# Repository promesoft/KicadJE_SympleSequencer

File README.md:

# KicadJE_SympleSequencer
Designed to fit the faceplate of a Hexinverter SympleSeq E2 faceplate from Re:Synthesis

# Purpose
1 - Match Hexinverter sch with Resynthesis panel

# Rev 2

# Status - Mouted - testing
## Initial 
| Stage  | Detail | Status |
| ------------- | ------------- | ------------- |
| create material  | sch/pcb | OK  |
| | gerber | OK |
| production  |   | ok |
|  | produced | ok |
|  | delivered | ok |

## Preliminary validation
| Test  | Detail | Status |
| ------------- | ------------- | ------------- |
| Initial Inspection | clock board| ok |
| Initial Inspection | control board | ok  |
| Initial Technical Test |  | 100n capacitors in series w output is replaced w 2k |
| Initial Product Test |  | 100n C101 capacitor parallel w 150k |
| Initial Product Test |  | ongoing |

## Secondary validation
| Test  | Detail | Status |
| ------------- | ------------- |------------- |
| Product Test | CV |  |
| Product Test | Gate | |
| Product Test | Clock internal |  |
| Product Test | Clock in |  |
| Product Test | Clock out |  |
| Product Test | Reset In/Button |  |
| Product Test | Hold In/Button |  |
| Quality | CV |  |
| Quality | Gate |  |
| Long Term Product Test |  | Good |
| Power Draw |  | 

## Errata
### Errata - clock
#### Series capacitors not working with reset (overloads CD4017)
 - replace w resistors (2k and 9k1 tested and working fine)
#### Hold not working 
 - Either swap R206 100k pullup with 22k-47k and R212 10k with 100k or tie hold to +12v works
### Errata - control
#### 

## Issues and Notes
### Clock
1 - diodes for hold input  
2 - diodes for reset input  
3 - Gate AND Clock for gate output to reset between gates - consider making a phase adjust for shorter/longer gates  
4 - OPEN resistor from Internal CLK to 4017 clock in (for use with Sequencer A that does not take slave clk input)
### Control
1 - switches still reversed  
2 - diode missing for reset  
3 - consider moving resistors from clk module to control as there is plenty of room  

# Schematics

# Pictures

# Rev 1

# Status - Installed in rack - tweaking
## Initial 
| Stage  | Detail | Status |
| ------------- | ------------- | ------------- |
| create material  | sch/pcb | OK  |
| | gerber | OK |
| production  |   | ok |
|  | produced | ok |
|  | delivered | ok |

## Preliminary validation
| Test  | Detail | Status |
| ------------- | ------------- | ------------- |
| Initial Inspection | clock board| ok - the jacks are 0,5-1mm too far away from the edge |
| Initial Inspection | control board | ok - see errata 3 |
| Initial Technical Test |  | ok |
| Initial Product Test |  | ok |

## Secondary validation
| Test  | Detail | Status |
| ------------- | ------------- |------------- |
| Product Test | CV | ok |
| Product Test | Gate | See errata 4|
| Product Test | Clock internal | ok - a bit slow |
| Product Test | Clock in | ok |
| Product Test | Clock out | ok - could need a buffer |
| Product Test | Reset In/Button | ok |
| Product Test | Hold In/Button | ok - needs debounce |
| Quality | CV | Good |
| Quality | Gate | No good - needs shorter pulses |
| Long Term Product Test |  | Good |
| Power Draw |  | 

## Errata
### Errata - clock
#### 1 - Missing slave clk function (add diode or buffer - consider val of  R204 on master)
#### 4 - Gate signal becomes glide if two adjacent notes are on (never goes to 0V - consider AC couple)
#### 5 - Hold works - but can be a bit jumpy if clocked faster than clk
#### 7 - Hold button needs debounce (47nF?)

### Errata - control
#### 2 - D310 not connected to G8 output
#### 3 - Switches upside down (still works just opposite the faceplate signs)
#### 6 - Switches in reset works one at the time. Mutliselect becomes strange (diode missing)

## Issues and Notes
### Clock
1 - Missing silk on Jacks

2 - 
### Control

## Vital Components
 - CD4017
 - LM555
 - Jack connectors: PJ-324M (important for the footprint)
# Schematics

# Pictures

# Inspiration from 
Counter module in https://github.com/promesoft/KicadJE_EffectsUnit1

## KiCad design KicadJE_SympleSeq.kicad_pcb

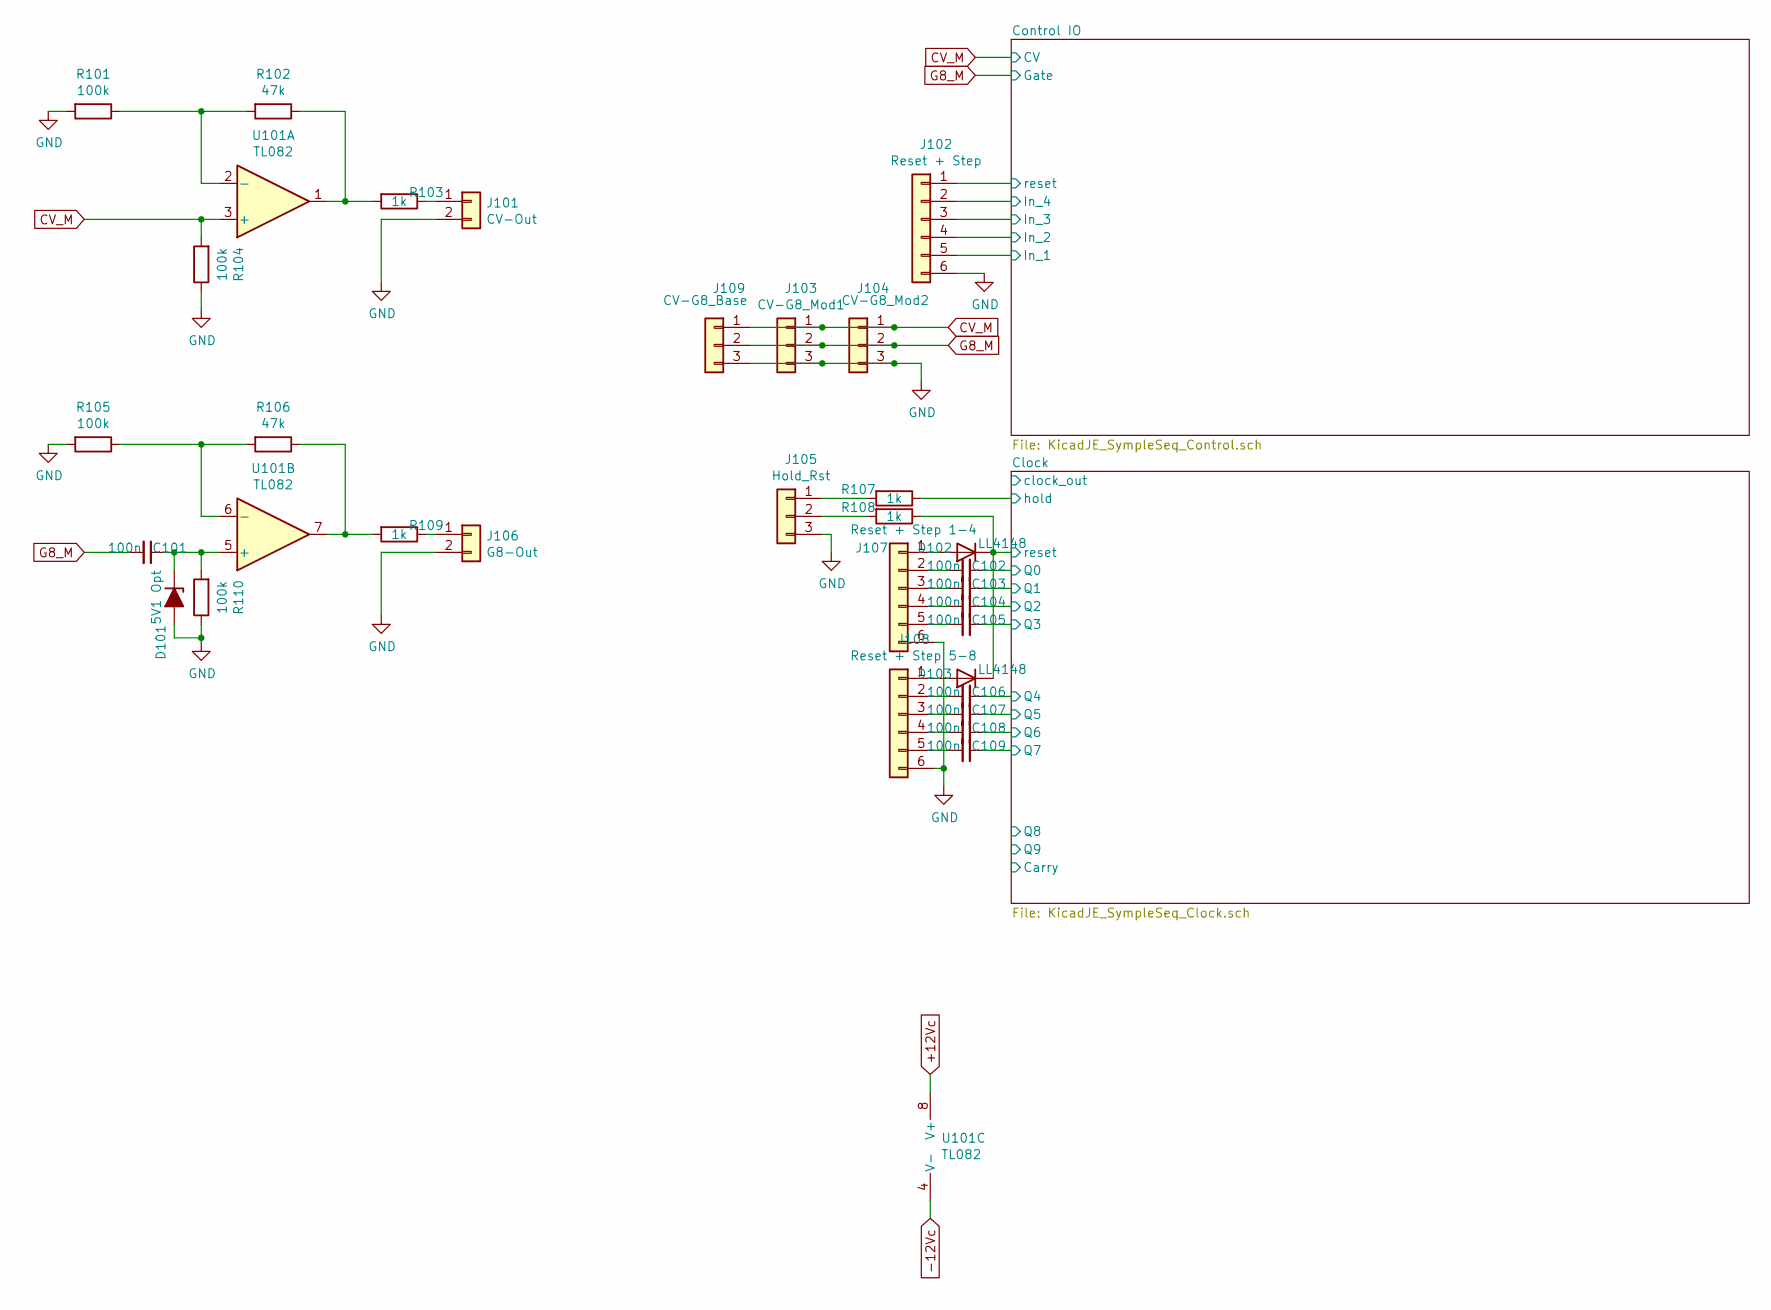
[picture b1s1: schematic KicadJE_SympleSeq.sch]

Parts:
C101, C102, C103, C104, C105, C106, C107, C108, C109: 100n; C_0805_AJ
D101: 5V1 Opt; D_MiniMELF
D102, D103: LL4148; D_MiniMELF
J101: CV-Out; PinHeader_1x02_P2.54mm_Vertical
J102: Reset + Step; PinHeader_1x06_P2.54mm_Vertical
J103: CV-G8_Mod1; PinHeader_1x03_P2.54mm_Vertical
J104: CV-G8_Mod2; PinHeader_1x03_P2.54mm_Vertical
J105: Hold_Rst; PinHeader_1x03_P2.54mm_Vertical
J106: G8-Out; PinHeader_1x02_P2.54mm_Vertical
J107: Reset + Step 1-4; PinHeader_1x06_P2.54mm_Vertical
J108: Reset + Step 5-8; PinHeader_1x06_P2.54mm_Vertical
J109: CV-G8_Base; PinHeader_1x03_P2.54mm_Vertical
R101, R104, R105, R110: 100k; R_0805_AJ
R102, R106: 47k; R_0805_AJ
R103, R107, R108, R109: 1k; R_0805_AJ
U101: TL082; AJ_SO-8_5.3x6.2mm_P1.27mm

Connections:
+12Vc: U101.8 (V+); also elsewhere on the board
-12Vc: U101.4 (V-); also elsewhere on the board
/Clock/Q0: C102.1; also elsewhere on the board
/Clock/Q1: C103.1; also elsewhere on the board
/Clock/Q2: C104.1; also elsewhere on the board
/Clock/Q3: C105.1; also elsewhere on the board
/Clock/Q4: C106.1; also elsewhere on the board
/Clock/Q5: C107.1; also elsewhere on the board
/Clock/Q6: C108.1; also elsewhere on the board
/Clock/Q7: C109.1; also elsewhere on the board
/Clock/hold: R107.1; also elsewhere on the board
/Clock/reset: D102.1 (K), D103.1 (K), R108.1; also elsewhere on the board
/Control IO/In_1: J102.5; also elsewhere on the board
/Control IO/In_2: J102.4; also elsewhere on the board
/Control IO/In_3: J102.3; also elsewhere on the board
/Control IO/In_4: J102.2; also elsewhere on the board
/Control IO/reset: J102.1; also elsewhere on the board
CV_M: J103.1, J104.1, J109.1, R104.2, U101.3 (+); also elsewhere on the board
G8_M: C101.2, J103.2, J104.2, J109.2; also elsewhere on the board
GND: D101.2 (A), J101.2, J102.6, J103.3, J104.3, J105.3, J106.2, J107.6, J108.6, J109.3, R101.2, R104.1, R105.2, R110.1; also elsewhere on the board
unnamed: C101.1, D101.1 (K), R110.2, U101.5 (+)
unnamed: C102.2, J107.2
unnamed: C103.2, J107.3
unnamed: C104.2, J107.4
unnamed: C105.2, J107.5
unnamed: C106.2, J108.2
unnamed: C107.2, J108.3
unnamed: C108.2, J108.4
unnamed: C109.2, J108.5
unnamed: D102.2 (A), J107.1
unnamed: D103.2 (A), J108.1
unnamed: J101.1, R103.1
unnamed: J105.1, R107.2
unnamed: J105.2, R108.2
unnamed: J106.1, R109.1
unnamed: R101.1, R102.2, U101.2 (-)
unnamed: R102.1, R103.2, U101.1
unnamed: R105.1, R106.2, U101.6 (-)
unnamed: R106.1, R109.2, U101.7

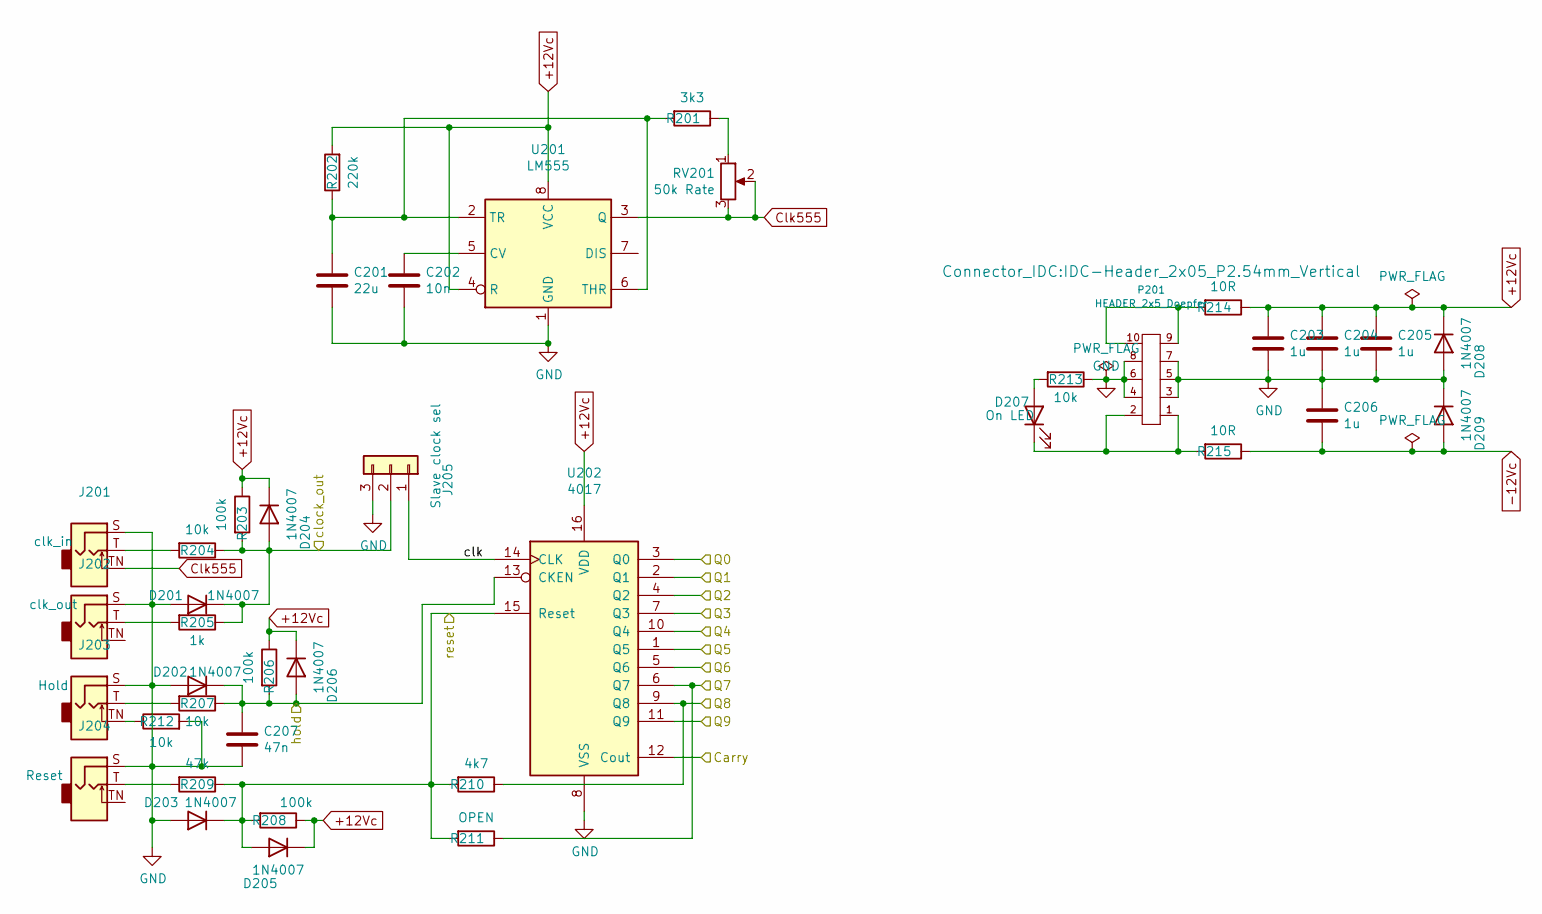
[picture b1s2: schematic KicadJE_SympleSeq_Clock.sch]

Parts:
C201: 22u; C_1206_3216Metric_Pad1.42x1.75mm_HandSolder
C202: 10n; C_0805_AJ
C203, C205: 1u; C_0805_AJ
C204, C206: 1u; C_1206_3216Metric_Pad1.42x1.75mm_HandSolder
C207: 47n; C_0805_AJ
D201, D202, D203, D204, D205, D206, D208, D209: 1N4007; D_MiniMELF
D207: On LED; D_0805_AJ
J201: clk_in; Jack_3.5mm_Ledino_KB3SPRS_Horizontal
J202: clk_out; Jack_3.5mm_Ledino_KB3SPRS_Horizontal
J203: Hold; Jack_3.5mm_Ledino_KB3SPRS_Horizontal
J204: Reset; Jack_3.5mm_Ledino_KB3SPRS_Horizontal
J205: Slave clock sel; PinHeader_1x03_P2.54mm_Vertical
P201: HEADER_2x5_Doepfer; IDC-Header_2x05_P2.54mm_Vertical
R201: 3k3; R_0805_AJ
R202: 220k; R_0805_AJ
R203, R206, R208: 100k; R_0805_AJ
R204, R207, R212, R213: 10k; R_0805_AJ
R205: 1k; R_0805_AJ
R209: 47k; R_0805_AJ
R210: 4k7; R_0805_AJ
R211: OPEN; R_0805_AJ
R214, R215: 10R; R_0805_AJ
RV201: 50k Rate; JST_EH_B3B-EH-A_1x03_P2.50mm_Vertical
U201: LM555; AJ_SO-8_5.3x6.2mm_P1.27mm
U202: 4017; SOIC-16_4.55x10.3mm_P1.27mm

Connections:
+12Vc: C203.1, C204.1, C205.1, D204.1 (K), D205.1 (K), D206.1 (K), D208.1 (K), R202.2, R203.1, R206.1, R208.1, R214.1, U201.4 (R), U201.8 (VCC), U202.16 (VDD); also elsewhere on the board
-12Vc: C206.2, D209.2 (A), R215.1; also elsewhere on the board
/Clock/Q0: U202.3 (Q0); also elsewhere on the board
/Clock/Q1: U202.2 (Q1); also elsewhere on the board
/Clock/Q2: U202.4 (Q2); also elsewhere on the board
/Clock/Q3: U202.7 (Q3); also elsewhere on the board
/Clock/Q4: U202.10 (Q4); also elsewhere on the board
/Clock/Q5: U202.1 (Q5); also elsewhere on the board
/Clock/Q6: U202.5 (Q6); also elsewhere on the board
/Clock/Q7: R211.1, U202.6 (Q7); also elsewhere on the board
/Clock/Q8: R210.1, U202.9 (Q8)
/Clock/clk: J205.1, U202.14 (CLK)
/Clock/clock_out: D201.1 (K), D204.2 (A), J205.2, R203.2, R204.1, R205.1
/Clock/hold: C207.1, D202.1 (K), D206.2 (A), R206.2, R207.1, U202.13 (CKEN); also elsewhere on the board
/Clock/reset: D203.1 (K), D205.2 (A), R208.2, R209.1, R210.2, R211.2, U202.15 (Reset); also elsewhere on the board
Clk555: J201.TN, RV201.2, RV201.3, U201.3 (Q)
GND: C201.2, C202.2, C203.2, C204.2, C205.2, C206.1, C207.2, D201.2 (A), D202.2 (A), D203.2 (A), D208.2 (A), D209.1 (K), J201.S, J202.S, J203.S, J204.S, J205.3, P201.3 (GND), P201.4 (GND), P201.5 (GND), P201.6 (GND), P201.7 (GND), P201.8 (GND), R212.2, R213.1, U201.1 (GND), U202.8 (VSS); also elsewhere on the board
unnamed: C201.1, R201.2, R202.1, U201.2 (TR), U201.6 (THR)
unnamed: C202.1, U201.5 (CV)
unnamed: D207.1 (K), P201.1 (-12), P201.2 (-12), R215.2
unnamed: D207.2 (A), R213.2
unnamed: J201.T, R204.2
unnamed: J202.T, R205.2
unnamed: J203.T, R207.2
unnamed: J203.TN, R212.1
unnamed: J204.T, R209.2
unnamed: P201.9 (+12), P201.10 (+12), R214.2
unnamed: R201.1, RV201.1

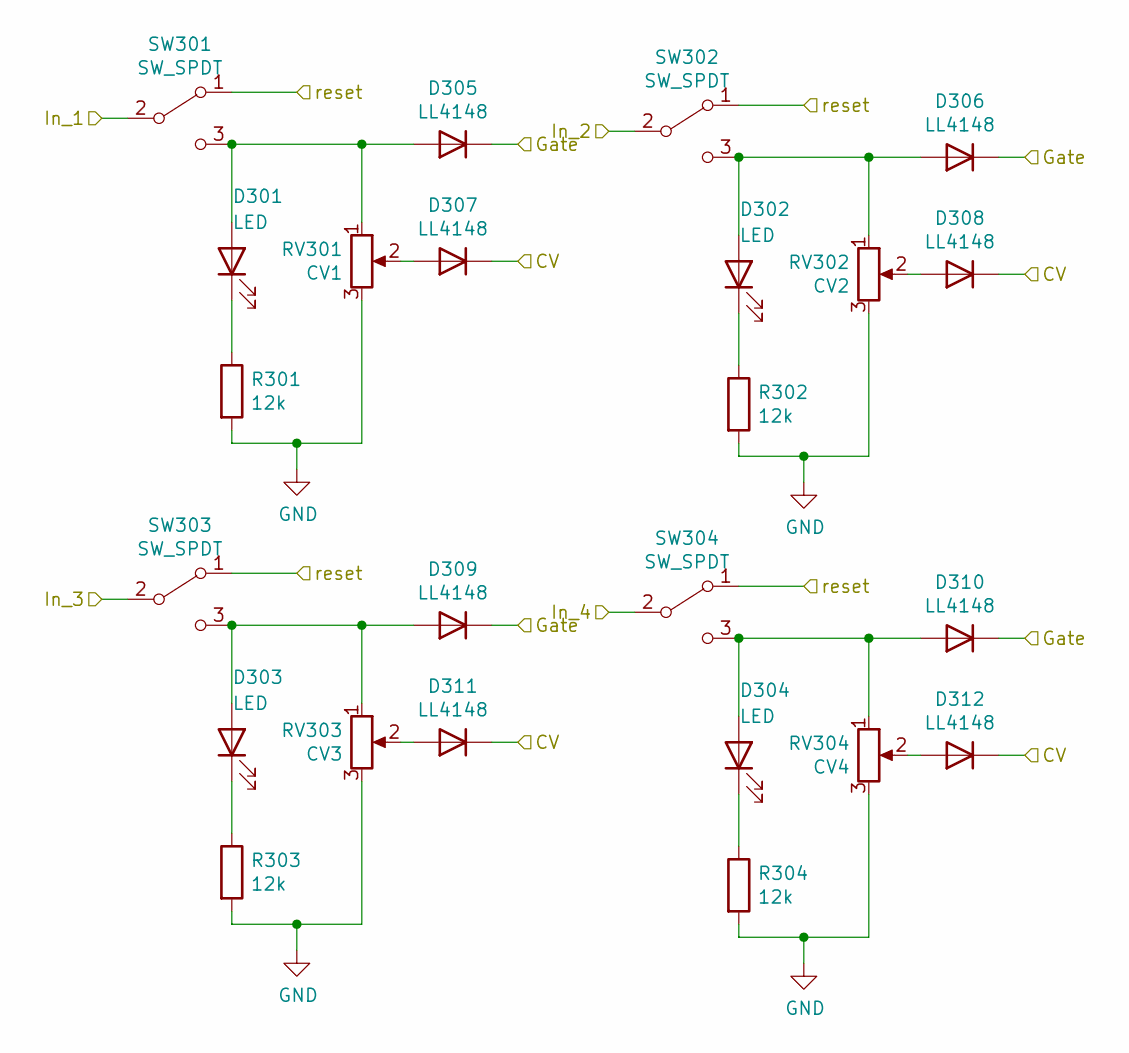
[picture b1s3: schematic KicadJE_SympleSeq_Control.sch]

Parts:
D301, D302, D303, D304: LED; LED_D3.0mm
D305, D306, D307, D308, D309, D310, D311, D312: LL4148; D_MiniMELF
R301, R302, R303, R304: 12k; R_0805_AJ
RV301: CV1; Potentiometer_China_RK09_Single_Vertical_AJ
RV302: CV2; Potentiometer_China_RK09_Single_Vertical_AJ
RV303: CV3; Potentiometer_China_RK09_Single_Vertical_AJ
RV304: CV4; Potentiometer_China_RK09_Single_Vertical_AJ
SW301, SW302, SW303, SW304: SW_SPDT; SP1MS1

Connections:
/Control IO/In_1: SW301.2 (B); also elsewhere on the board
/Control IO/In_2: SW302.2 (B); also elsewhere on the board
/Control IO/In_3: SW303.2 (B); also elsewhere on the board
/Control IO/In_4: SW304.2 (B); also elsewhere on the board
/Control IO/reset: SW301.1 (A), SW302.1 (A), SW303.1 (A), SW304.1 (A); also elsewhere on the board
CV_M: D307.1 (K), D308.1 (K), D311.1 (K), D312.1 (K); also elsewhere on the board
G8_M: D305.1 (K), D306.1 (K), D309.1 (K), D310.1 (K); also elsewhere on the board
GND: R301.2, R302.2, R303.2, R304.2, RV301.3, RV302.3, RV303.3, RV304.3; also elsewhere on the board
unnamed: D301.1 (K), R301.1
unnamed: D301.2 (A), D305.2 (A), RV301.1, SW301.3 (C)
unnamed: D302.1 (K), R302.1
unnamed: D302.2 (A), D306.2 (A), RV302.1, SW302.3 (C)
unnamed: D303.1 (K), R303.1
unnamed: D303.2 (A), D309.2 (A), RV303.1, SW303.3 (C)
unnamed: D304.1 (K), R304.1
unnamed: D304.2 (A), D310.2 (A), RV304.1, SW304.3 (C)
unnamed: D307.2 (A), RV301.2
unnamed: D308.2 (A), RV302.2
unnamed: D311.2 (A), RV303.2
unnamed: D312.2 (A), RV304.2

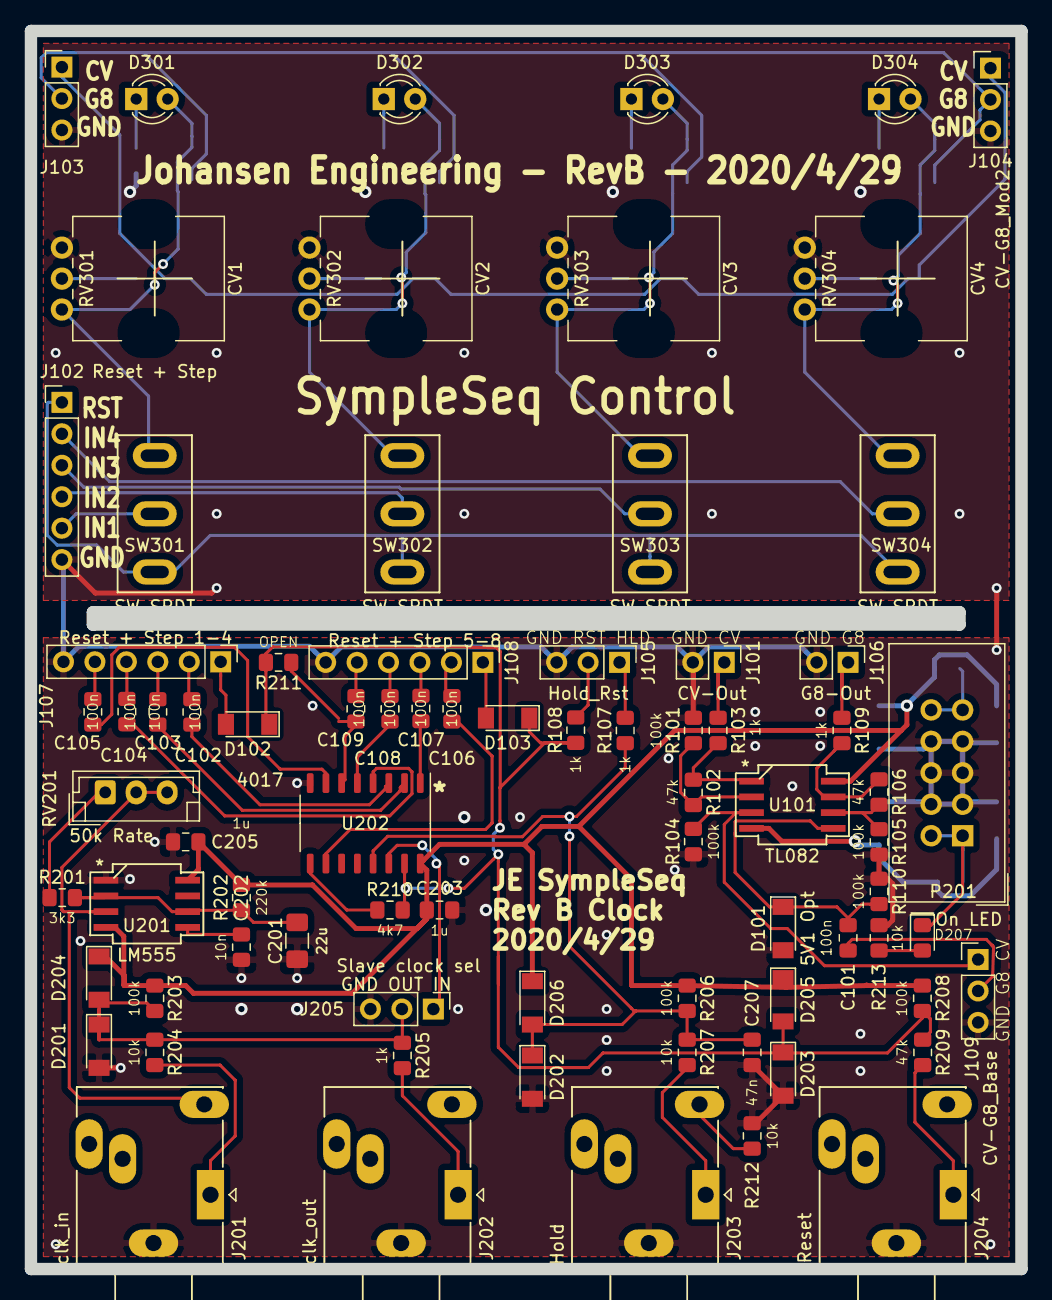
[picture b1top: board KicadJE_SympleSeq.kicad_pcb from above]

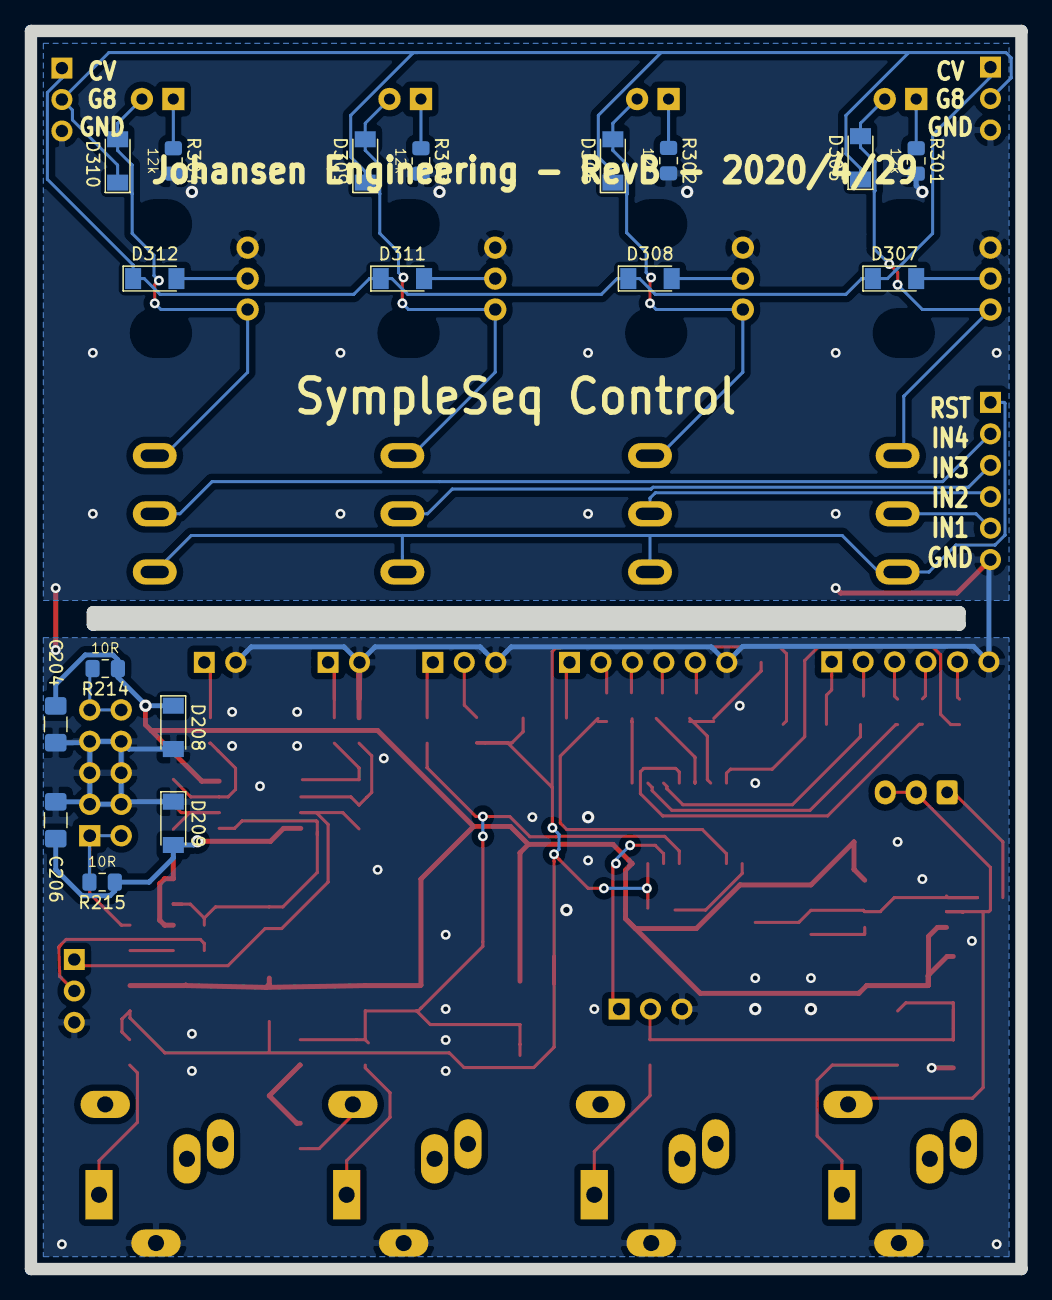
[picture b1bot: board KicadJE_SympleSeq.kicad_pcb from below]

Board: 2 copper layers, 80.0 x 100.0 mm, 96 parts (18 on the bottom side), 66 nets.

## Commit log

2019-09-28 init
2019-09-29 Counter w protection
2019-09-29 555 done sch
2019-09-29 Hierarchical pins
2019-09-29 Sch taking form
2019-09-29 pin headers
2019-09-30 base circuit done
2019-09-30 Annotate #1
2019-09-30 control module PCB init
2019-09-30 Control Done PCB
2019-09-30 Init Clock board
2019-09-30 clock board done
2019-09-30 Gerber
2019-12-11 Update KicadJE_SympleSeq.kicad_pcb-bak
2020-04-27 RevA -> RevB
2020-04-27 RevB Initiated
2020-04-27 slave clk - debounce hold etc
2020-04-27 RevB updates
2020-04-29 Diode prot from LED->1N4007
2020-04-29 ERC Rev B
2020-04-29 AJ Footprints
2020-04-29 AJ footprints updated
2020-04-29 D310 connected
2020-04-29 hold/rst
2020-04-29 Updated PCB rev B
2020-04-29 Update KicadJE_SympleSeq_Control.sch
    Fix LED error 0805 -> LED_THT:LED_D3.0mm
2020-04-29 PCB rdy for DRC
2020-04-29 Fix 3mm LED
2020-04-29 Unconnected fix
2020-04-29 move BOM to rev A
2020-04-29 RevB Gerber
2020-04-29 Fix few things for RevB (2)
2020-04-29 RevB2
    fix Jack a bit further to the front
    labeling
    Minor adj to fix courtyard overlaps
2021-05-02 rename
2021-05-03 pict etc
